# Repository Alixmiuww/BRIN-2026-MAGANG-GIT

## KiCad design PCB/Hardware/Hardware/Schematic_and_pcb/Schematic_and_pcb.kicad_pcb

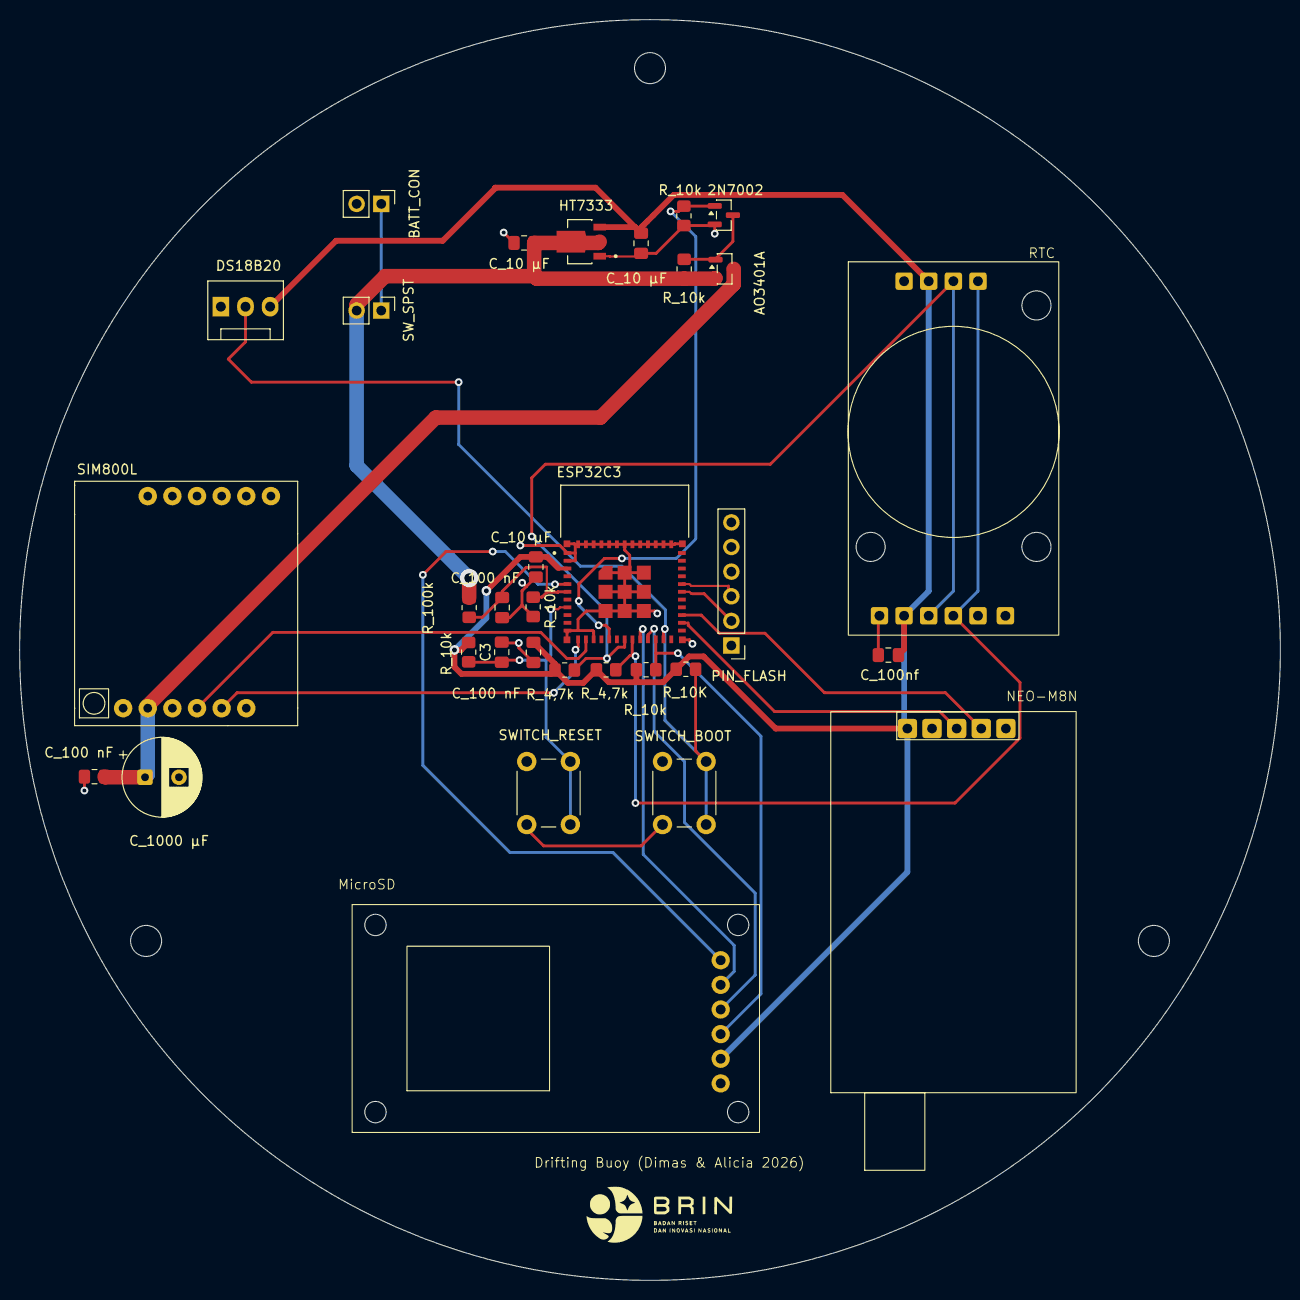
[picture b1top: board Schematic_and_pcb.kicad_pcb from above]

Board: 2 copper layers, 130.0 x 130.0 mm, 35 parts (0 on the bottom side), 22 nets.

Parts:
2N7002: 2N7002; SOT-23
AO3401A: AO3401A; SOT-23
BATT_CON: Battery Conn; PinHeader_1x02_P2.54mm_Vertical
C3: 1 µF; C_0805_2012Metric_Pad1.18x1.45mm_HandSolder
C_10 µF, C_10 µF#2, C_10 µF#3: 10 µF; C_0805_2012Metric_Pad1.18x1.45mm_HandSolder
C_100 nF, C_100 nF#2, C_100 nF#3, C_100nf: 100 nF; C_0805_2012Metric_Pad1.18x1.45mm_HandSolder
C_1000 µF: 1000 µF; CP_Radial_D8.0mm_P3.50mm
DS18B20: DS18B20; FanPinHeader_1x03_P2.54mm_Vertical
ESP32C3: ESP32-C3-MINI-1-N4; XCVR_ESP32-C3-MINI-1-N4
H1, H2, H3: MountingHole; MountingHole_3.2mm_M3
HT7333: HT7333; IC_HT7333
MicroSD: modul sdcard
NEO-M8N: Untitled
PIN_FLASH: PIN_FLASH; PinHeader_1x06_P2.54mm_Vertical
RTC: DS3231M; DS3231
R_4,7k, R_4,7k#2: 4.7 kΩ; R_0805_2012Metric_Pad1.20x1.40mm_HandSolder
R_10K, R_10k, R_10k#3: 10k; R_0805_2012Metric_Pad1.20x1.40mm_HandSolder
R_10k#2, R_100k: 100 kΩ; R_0805_2012Metric_Pad1.20x1.40mm_HandSolder
R_10k#4, R_10k#5: 10 kΩ; R_0805_2012Metric_Pad1.20x1.40mm_HandSolder
SIM800L: SIM800L-CORE
SWITCH_BOOT: SW_BOOT; SW_PUSH_6mm
SWITCH_RESET: SW_RESET; SW_PUSH_6mm
SW_SPST: SW_SPST; PinHeader_1x02_P2.54mm_Vertical

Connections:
+3.3V: C_10 µF#2.1, C_10 µF#3.1, C_100 nF#3.1, C_100nf.2, DS18B20.3 (V_{DD}), ESP32C3.3 (3V3), HT7333.3 (VOUT), MicroSD.VCC, NEO-M8N.VCC, RTC.VCC, R_4,7k.1, R_4,7k#2.1, R_10K.1, R_10k.1, R_10k#3.1
/I2C.SCL: ESP32C3.19 (IO5), RTC.SCL, R_4,7k#2.2
/I2C.SDA: ESP32C3.18 (IO4), RTC.SDA, R_4,7k.2
/MCU_Core/EN: C3.1, ESP32C3.8 (EN), R_10k#3.2, SWITCH_RESET.1
/MCU_Core/GATE_CTRL: 2N7002.1 (G), ESP32C3.16 (IO10), R_10k#5.1
/MCU_Core/GPS_RX_MCU: ESP32C3.26 (IO18), NEO-M8N.TXD
/MCU_Core/GPS_TX_MCU: ESP32C3.27 (IO19), NEO-M8N.RXD
/MCU_Core/MCU_BOOT: DS18B20.2 (DQ), ESP32C3.23 (IO9), R_10K.2, SWITCH_BOOT.1
/MCU_Core/RXD0: ESP32C3.31 (TXD0), PIN_FLASH.3
/MCU_Core/SD_CS: ESP32C3.5 (IO2), MicroSD.CS (~CS)
/MCU_Core/SIM_RX_MCU: ESP32C3.12 (IO0), SIM800L.5 (TXD)
/MCU_Core/SIM_TX_MCU: ESP32C3.13 (IO1), SIM800L.4 (RXD)
/MCU_Core/SPI_MISO: ESP32C3.22 (IO8), MicroSD.MISO, R_10k.2
/MCU_Core/SPI_MOSI: ESP32C3.21 (IO7), MicroSD.MOSI
/MCU_Core/SPI_SCK: ESP32C3.20 (IO6), MicroSD.SCK
/MCU_Core/TXD0: ESP32C3.30 (RXD0), PIN_FLASH.2
/MCU_Core/VBAT_ADC: C_100 nF.1, ESP32C3.6 (IO3), R_10k#2.1, R_100k.2
GND: 2N7002.2 (S), BATT_CON.2, C3.2, C_10 µF.2, C_10 µF#2.2, C_10 µF#3.2, C_100 nF.2, C_100 nF#2.2, C_100 nF#3.2, C_100nf.1, C_1000 µF.2, DS18B20.1 (GND), ESP32C3.1 (GND), ESP32C3.2 (GND), ESP32C3.11 (GND), ESP32C3.14 (GND), ESP32C3.36 (GND), ESP32C3.37 (GND), ESP32C3.38 (GND), ESP32C3.39 (GND), ESP32C3.40 (GND), ESP32C3.41 (GND), ESP32C3.42 (GND), ESP32C3.43 (GND), ESP32C3.44 (GND), ESP32C3.45 (GND), ESP32C3.46 (GND), ESP32C3.47 (GND), ESP32C3.48 (GND), ESP32C3.49_1 (GND), ESP32C3.49_2 (GND), ESP32C3.49_3 (GND), ESP32C3.49_4 (GND), ESP32C3.49_5 (GND), ESP32C3.49_6 (GND), ESP32C3.49_7 (GND), ESP32C3.49_8 (GND), ESP32C3.49_9 (GND), ESP32C3.50 (GND), ESP32C3.51 (GND), ESP32C3.52 (GND), ESP32C3.53 (GND), HT7333.1 (GND), MicroSD.GND, NEO-M8N.GND, PIN_FLASH.5, PIN_FLASH.6, RTC.GND, R_10k#2.2, R_10k#5.2, SIM800L.6 (GND), SWITCH_BOOT.2, SWITCH_RESET.2
unnamed: BATT_CON.1, SW_SPST.1 (A)
unnamed: 2N7002.3 (D), AO3401A.1 (G), R_10k#4.1
V_BAT: AO3401A.2 (S), C_10 µF.1, HT7333.2 (VIN), R_10k#4.2, R_100k.1, SW_SPST.2 (B)
V_SWITCHED: AO3401A.3 (D), C_100 nF#2.1, C_1000 µF.1, SIM800L.2 (VCC)

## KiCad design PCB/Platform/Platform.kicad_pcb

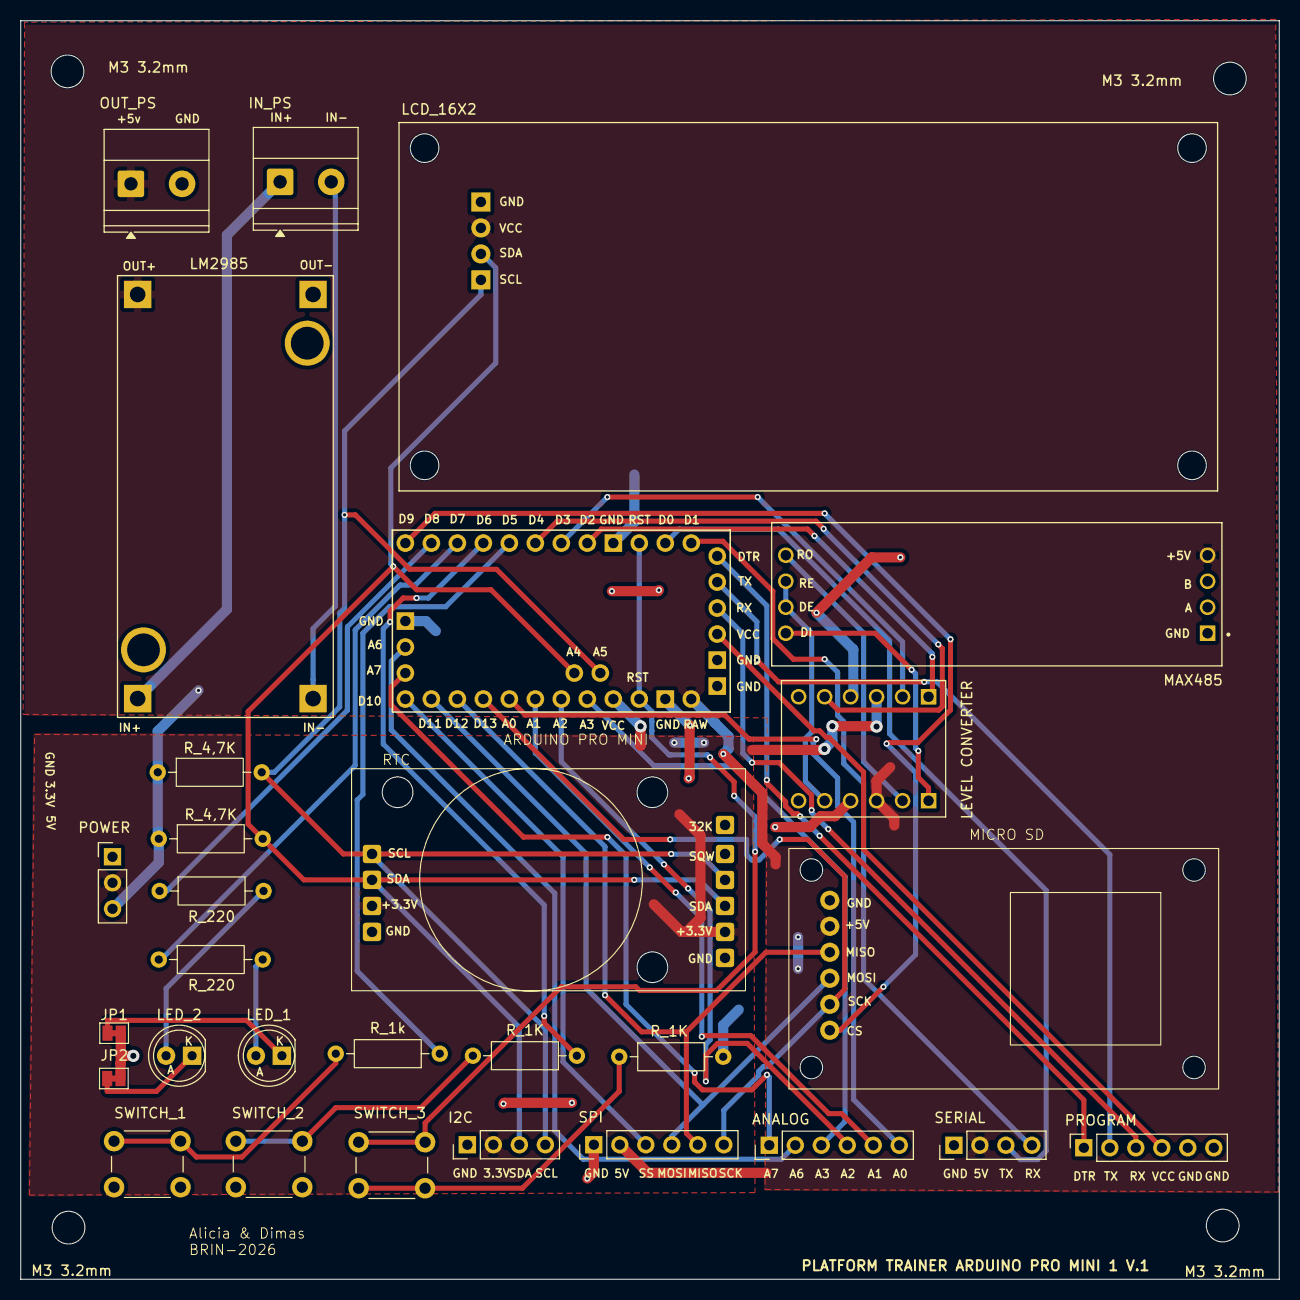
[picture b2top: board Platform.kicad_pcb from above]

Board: 2 copper layers, 123.0 x 123.0 mm, 33 parts (0 on the bottom side), 42 nets.

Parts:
A2: Clone_Pro_Mini_Socket
ANALOG: Pin_Analog; PinHeader_1x06_P2.54mm_Vertical
I2C: Pin_I2C_eksternal; PinHeader_1x04_P2.54mm_Vertical
IN_PS: Conn_01x02_Pin; TerminalBlock_Phoenix_MKDS-1,5-2_1x02_P5.00mm_Horizontal
JP1, JP2: SolderJumper_2_Bridged; SolderJumper-2_P1.3mm_Bridged_Pad1.0x1.5mm
LCD_16X2: Pin_LCD; MODULE_LCD-16X2
LED_1, LED_2: LED; LED_D5.0mm
LEVEL CONVERTER: BOB-12009; CONV_BOB-12009
LM2985: LM2596; CONV_MC00100
M3 3.2mm, M3 3.2mm#2, M3 3.2mm#3, M3 3.2mm#4: MountingHole_3.2mm_M3
MAX485: MAX485_MODULE_5V_LOGIC_TLL_TO_RS-485_CONVERTER; MODULE_MAX485_MODULE_5V_LOGIC_TLL_TO_RS-485_CONVERTER
MICRO SD: MICRO SDCARD; modul sdcard
OUT_PS: Conn_01x02_Pin; TerminalBlock_Phoenix_MKDS-1,5-2_1x02_P5.00mm_Horizontal
POWER: PWR External; PinHeader_1x03_P2.54mm_Vertical
PROGRAM: Program; PinSocket_1x06_P2.54mm_Vertical
RTC: PIN_RTC; DS3231
R_1K, R_1K#2, R_1k: 1kΩ; R_Axial_DIN0207_L6.3mm_D2.5mm_P10.16mm_Horizontal
R_4,7K, R_4,7K#2: 4.7k; R_Axial_DIN0207_L6.3mm_D2.5mm_P10.16mm_Horizontal
R_220, R_220#2: 220Ω; R_Axial_DIN0207_L6.3mm_D2.5mm_P10.16mm_Horizontal
SERIAL: Pin_SERIAL; PinHeader_1x04_P2.54mm_Vertical
SPI: Pin_SPI_1; PinHeader_1x06_P2.54mm_Vertical
SWITCH_1, SWITCH_2: SW_Push; SW_PUSH_6mm
SWITCH_3: RST; SW_PUSH_6mm

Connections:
+3.3V: A2.Vcc1 (Vcc), I2C.2, LEVEL CONVERTER.LV, POWER.2, RTC.VCC (Pin_2)
+5V: A2.RAW, LCD_16X2.VCC (Pin_2), LEVEL CONVERTER.HV, LM2985.OUT+, MAX485.4 (VCC), MICRO SD.VCC (Pin_3), OUT_PS.1, POWER.3, R_4,7K.1, R_4,7K#2.1, SERIAL.2, SPI.2
/A0: A2.A0, ANALOG.6
/A1: A2.A1, ANALOG.5
/A2: A2.A2, ANALOG.4
/A3: A2.A3, ANALOG.3
/A6: A2.A6, ANALOG.2
/A7: A2.A7, ANALOG.1
/I2C_UART_BUS.RX: A2.D1 (D1/TX), SERIAL.4
/I2C_UART_BUS.SCL: A2.A5 (A5/SCL), I2C.4, LCD_16X2.SCL (Pin_4), RTC.SCL (Pin_4), R_4,7K#2.2
/I2C_UART_BUS.SDA: A2.A4 (A4/SDA), I2C.3, LCD_16X2.SDA (Pin_3), RTC.SDA (Pin_3), R_4,7K.2
/I2C_UART_BUS.TX: A2.D0 (D0/RX), SERIAL.3
/IO_BUS.BTN1: A2.D5, R_1k.1
/IO_BUS.BTN2: A2.D6, R_1K.1
/IO_BUS.LED1: A2.D7, R_220#2.1
/IO_BUS.LED2: A2.D8, R_220.1
/RS485_CTRL: A2.D4, LEVEL CONVERTER.LV3
/RS485_HV1: LEVEL CONVERTER.HV1, MAX485.HV1 (RO)
/RS485_HV2: LEVEL CONVERTER.HV2, MAX485.HV2 (DI)
/RS485_HV3: LEVEL CONVERTER.HV3, MAX485.HV3 (DE)
/RS485_RX: A2.D2 (D2_INT0), LEVEL CONVERTER.LV1
/RS485_TX: A2.D3 (D3_INT1), LEVEL CONVERTER.LV2
/RST: A2.RST1 (RESET), A2.RST2 (RESET), SWITCH_3.1
/SPI_BUS.MISO: A2.D12 (D12_MISO), MICRO SD.MISO (Pin_6), SPI.5
/SPI_BUS.MOSI: A2.D11 (D11_MOSI), MICRO SD.MOSI (Pin_2), SPI.4
/SPI_BUS.SCK: A2.D13 (D13_SCK), MICRO SD.SCK (Pin_4), SPI.6
/SPI_BUS.SD_CS: A2.D9, MICRO SD.CS (Pin_1)
/SPI_BUS.SS: A2.D10 (D10_CS), SPI.3
/V_RAW: IN_PS.1, LM2985.IN+
GND: A2.GND1 (GND), A2.GND2 (GND), A2.GND3 (GND), A2.GND4 (GND), A2.GND5 (GND), I2C.1, JP1.2 (B), JP2.2 (B), LCD_16X2.GND (Pin_1), LEVEL CONVERTER.GND_1 (GND), LEVEL CONVERTER.GND_2 (GND), LM2985.OUT-, MAX485.1 (GND), MICRO SD.GND (Pin_5), OUT_PS.2, POWER.1, PROGRAM.5, PROGRAM.6, RTC.GND (Pin_1), R_1K#2.2, SERIAL.1, SPI.1, SWITCH_1.2, SWITCH_2.2
unnamed: A2.DTR (~DTR), PROGRAM.1
unnamed: LED_1.2 (A), R_220#2.2
unnamed: JP1.1 (A), LED_1.1 (K)
unnamed: LED_2.2 (A), R_220.2
unnamed: JP2.1 (A), LED_2.1 (K)
unnamed: A2.TXO, PROGRAM.2
unnamed: A2.RXI, PROGRAM.3
unnamed: A2.Vcc2 (Vcc), PROGRAM.4
unnamed: IN_PS.2, LM2985.IN-
unnamed: R_1k.2, SWITCH_1.1
unnamed: R_1K.2, SWITCH_2.1
unnamed: R_1K#2.1, SWITCH_3.2

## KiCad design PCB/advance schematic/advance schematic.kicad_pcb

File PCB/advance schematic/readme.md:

# ESP32 Controller — Schematic Documentation

## 1. Deskripsi Proyek

Proyek ini merupakan pengembangan rangkaian kontroler berbasis **ESP32-DevKitC-32E** yang menggunakan dua modul joystick analog, beberapa tombol kontrol, sensor GY-521 (MPU6050), LED RGB, serta rangkaian pemantauan tegangan baterai.

Rangkaian dirancang sebagai perangkat input untuk membaca pergerakan joystick, menerima perintah dari tombol, dan menyediakan data sensor untuk kebutuhan sistem kendali elektronik, seperti robot atau kendaraan berbasis mikrokontroler.

## 2. Fitur Utama

- **Dual Analog Joystick:** Membaca input sumbu X dan Y dari dua modul joystick.
- **Button Control:** Menyediakan tombol untuk kontrol drop, pickup, peningkatan kecepatan, penurunan kecepatan, dan pemilihan mode.
- **IMU Sensor:** Menggunakan GY-521 berbasis MPU6050 untuk membaca percepatan dan kecepatan sudut.
- **Battery Voltage Monitoring:** Menyediakan rangkaian pembagi tegangan untuk membaca tegangan baterai melalui ADC ESP32.
- **RGB LED Indicator:** Menyediakan indikator visual melalui LED RGB.
- **ESP32 Microcontroller:** Bertindak sebagai pusat pembacaan input dan pemrosesan data kontrol.

## 3. Komponen yang Digunakan

| Komponen | Fungsi |
|---|---|
| ESP32-DevKitC-32E | Mikrokontroler utama |
| 2× Joystick Module | Input analog sumbu X dan Y |
| 6× Push Button | Input perintah kontrol |
| GY-521 (MPU6050) | Sensor gerak berbasis IMU |
| LED RGB | Indikator status |
| Resistor 10 kΩ | Jaringan tombol dan pembagi tegangan |
| Resistor 100 kΩ | Pembagi tegangan pemantauan baterai |
| Konektor baterai | Input tegangan baterai |
| Sakelar | Pengendalian jalur rangkaian sesuai skematik |

## 4. Pemetaan Pin ESP32

### A. Input Joystick

| Sinyal | GPIO ESP32 |
|---|---:|
| JOY.VRx1 | GPIO 33 |
| JOY.VRy1 | GPIO 32 |
| JOY.VRx2 | GPIO 35 |
| JOY.VRy2 | GPIO 34 |

GPIO 32, 33, 34, dan 35 digunakan untuk membaca sinyal analog dari kedua joystick. GPIO 34 dan GPIO 35 merupakan pin input-only sehingga sesuai untuk pembacaan ADC.

### B. Tombol Kontrol

| Sinyal | GPIO ESP32 | Fungsi |
|---|---:|---|
| CONTROL.drop | GPIO 13 | Perintah drop |
| CONTROL.plck | GPIO 14 | Perintah pickup |
| CONTROL.up | GPIO 26 | Menaikkan kecepatan |
| CONTROL.down | GPIO 25 | Menurunkan kecepatan |
| SW.mode.joy1 | GPIO 18 | Pemilihan mode joystick |
| SW.mode.sensor | GPIO 19 | Pemilihan mode sensor |

**Catatan:** Pemetaan pin mengikuti label jaringan pada skematik. Pastikan konfigurasi pin pada program sesuai dengan hasil akhir desain PCB.

### C. Sensor GY-521 (MPU6050)

| Sinyal | Koneksi |
|---|---|
| VCC | +5 V sesuai skematik |
| GND | GND |
| SDA | Jalur I²C SDA |
| SCL | Jalur I²C SCL |
| AD0 | Tidak terhubung |
| INT | Tidak terhubung |
| XCL dan XDA | Tidak terhubung |

Jalur SDA dan SCL dihubungkan ke GPIO ESP32 yang ditentukan dalam konfigurasi perangkat lunak. Pin AD0 yang tidak terhubung umumnya membuat alamat I²C MPU6050 berada pada `0x68`, tetapi kondisi pin perlu dipastikan pada modul yang digunakan.

### D. LED RGB

LED RGB digunakan sebagai indikator status perangkat. Setiap kanal warna terhubung ke jalur GPIO melalui rangkaian pada skematik.

**Catatan:** Nomor GPIO untuk setiap kanal LED perlu dipastikan dari label net dan koneksi lengkap pada skematik sebelum diimplementasikan dalam kode.

### E. Pemantauan Tegangan Baterai

Rangkaian pemantauan tegangan menggunakan resistor pembagi tegangan untuk menyesuaikan tegangan baterai dengan rentang input ADC ESP32.

Nilai tegangan input dapat dihitung menggunakan:

`V_baterai = V_ADC × (R_atas + R_bawah) / R_bawah`

Rumus tersebut berlaku untuk pembagi tegangan standar, dengan `R_atas` terhubung dari baterai positif ke titik ADC dan `R_bawah` terhubung dari titik ADC ke GND.

**Penting:** Nilai resistor dan jalur pada skematik perlu diverifikasi. Pastikan tegangan yang masuk ke pin ADC tidak melebihi batas aman ESP32. Jika ingin mengukur tegangan baterai di atas rentang ADC, gunakan pembagi tegangan yang sesuai.

## 5. Prinsip Kerja Sistem

1. ESP32 dinyalakan melalui sumber daya yang sesuai.
2. Kedua joystick menghasilkan sinyal analog sesuai posisi sumbu X dan Y.
3. ESP32 membaca perubahan sinyal analog melalui ADC.
4. Tombol memberikan perintah digital untuk drop, pickup, pengaturan kecepatan, dan pemilihan mode.
5. Sensor MPU6050 menyediakan data percepatan dan kecepatan sudut melalui komunikasi I²C.
6. Rangkaian pembagi tegangan menyediakan sinyal yang mewakili tegangan baterai untuk dipantau ESP32.
7. Data input diproses oleh firmware untuk menentukan perintah kontrol dan status sistem.

## 6. Perangkat Lunak

Firmware dapat dikembangkan menggunakan Arduino IDE atau PlatformIO dengan framework Arduino.

Library yang dapat digunakan:
- `Arduino.h` — fungsi dasar ESP32.
- `Wire.h` — komunikasi I²C.
- Library MPU6050 yang kompatibel — pembacaan data IMU.

## 7. Catatan Desain dan Pengujian

Sebelum rangkaian diproduksi atau digunakan, lakukan pemeriksaan berikut:

- Verifikasi semua koneksi daya, GND, dan GPIO.
- Pastikan setiap tombol memiliki logika input yang sesuai dengan konfigurasi resistor.
- Periksa apakah resistor 10 kΩ pada jaringan tombol berfungsi sebagai pull-up atau pull-down sesuai kebutuhan.
- Pastikan tegangan keluaran joystick tidak melebihi batas ADC ESP32.
- Verifikasi konfigurasi pembagi tegangan baterai dan batas tegangan ADC.
- Pastikan LED RGB memiliki resistor pembatas arus yang sesuai untuk setiap kanal.
- Periksa alamat I²C MPU6050 dan jalur SDA/SCL menggunakan pemindaian I²C.
- Lakukan pemeriksaan ERC pada skematik dan DRC pada layout PCB sebelum fabrikasi.

## 8. Kesimpulan

Rangkaian ini dirancang sebagai kontroler berbasis ESP32 dengan input joystick analog, tombol digital, sensor IMU, indikator RGB, dan pemantauan tegangan baterai. Integrasi komponen tersebut memungkinkan ESP32 mengumpulkan berbagai input untuk diproses menjadi perintah kendali. Validasi koneksi daya, pemetaan GPIO, dan rangkaian ADC perlu dilakukan sebelum implementasi perangkat lunak dan pembuatan PCB.

## 9. Schematic Rancangan

## 10. PCB Rancangan

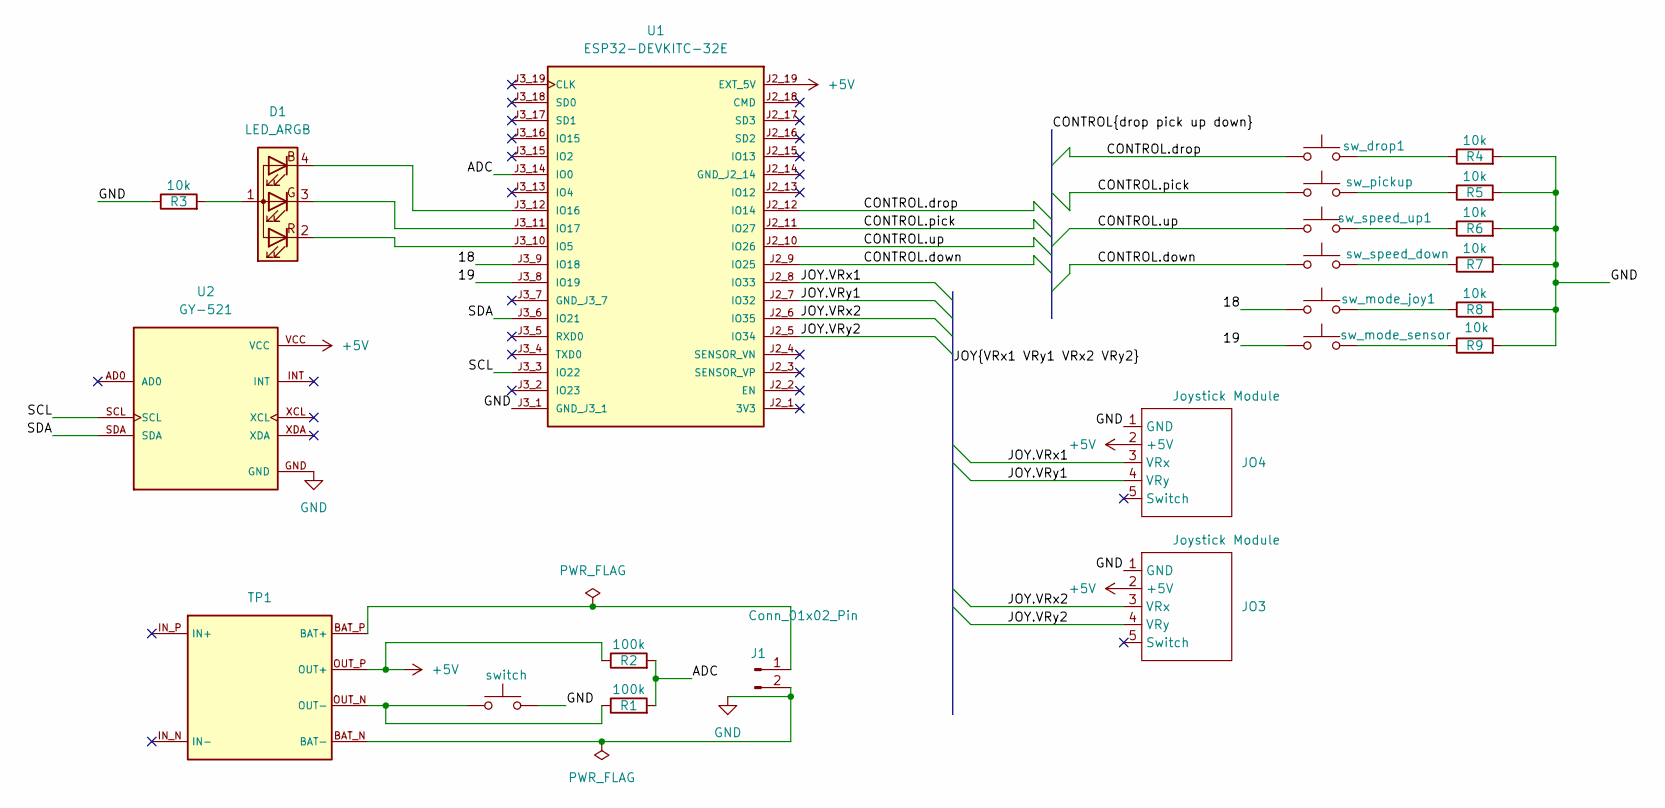
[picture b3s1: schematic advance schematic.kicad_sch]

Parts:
D1: LED_ARGB; LED_D5.0mm-4_RGB_Wide_Pins
J1: Conn_01x02_Pin; JST_EH_B2B-EH-A_1x02_P2.50mm_Vertical
JO3, JO4: Joystick Module; Module joystick
R1, R2: 100k; R_Axial_DIN0204_L3.6mm_D1.6mm_P1.90mm_Vertical
R3, R4, R5, R6, R7, R8, R9: 10k; R_Axial_DIN0204_L3.6mm_D1.6mm_P1.90mm_Vertical
SW2: sw_pickup; SW_PUSH_6mm
SW3: sw_speed_down; SW_PUSH_6mm
SW4: sw_mode_sensor; SW_PUSH_6mm
SW5: switch; SW_DIP_SPSTx01_Slide_6.7x4.1mm_W7.62mm_P2.54mm_LowProfile
TP1: MODULE_TP4056_MICRO-USB_CHARGER_-_1A
U1: ESP32-DEVKITC-32E; MODULE_ESP32-DEVKITC-32E; PARTREV 1.4
U2: GY-521; MODULE_GY-521; PARTREV NA
sw_drop1: SW_Push; SW_PUSH_6mm
sw_mode_joy1: SW_Push; SW_PUSH_6mm
sw_speed_up1: SW_Push; SW_PUSH_6mm

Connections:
+5V: JO3.2 (+5V), JO4.2 (+5V), R2.1, TP1.OUT_P (OUT+), U1.J2_19 (EXT_5V), U2.VCC
/18: U1.J3_9 (IO18), sw_mode_joy1.1
/19: SW4.1, U1.J3_8 (IO19)
/<NO NET>: D1.2 (RK), D1.4 (BK), U1.J3_10 (IO5), U1.J3_12 (IO16)
/ADC: R1.2, R2.2, U1.J3_14 (IO0)
/CONTROL.down: SW3.1, U1.J2_9 (IO25)
/CONTROL.drop: U1.J2_12 (IO14), sw_drop1.1
/CONTROL.pick: SW2.1, U1.J2_11 (IO27)
/CONTROL.up: U1.J2_10 (IO26), sw_speed_up1.1
/JOY.VRx1: JO4.3 (VRx), U1.J2_8 (IO33)
/JOY.VRx2: JO3.3 (VRx), U1.J2_6 (IO35)
/JOY.VRy1: JO4.4 (VRy), U1.J2_7 (IO32)
/JOY.VRy2: JO3.4 (VRy), U1.J2_5 (IO34)
/SCL: U1.J3_3 (IO22), U2.SCL
/SDA: U1.J3_6 (IO21), U2.SDA
GND: J1.2, JO3.1 (GND), JO4.1 (GND), R3.1, R4.2, R5.2, R6.2, R7.2, R8.2, R9.2, SW5.2, TP1.BAT_N (BAT-), U1.J3_1 (GND_J3_1), U2.GND
unnamed: D1.1 (A), R3.2
unnamed: D1.3 (GK), U1.J3_11 (IO17)
unnamed: J1.1, TP1.BAT_P (BAT+)
unnamed: R4.1, sw_drop1.2
unnamed: R5.1, SW2.2
unnamed: R6.1, sw_speed_up1.2
unnamed: R7.1, SW3.2
unnamed: R8.1, sw_mode_joy1.2
unnamed: R9.1, SW4.2
unnamed: R1.1, SW5.1, TP1.OUT_N (OUT-)

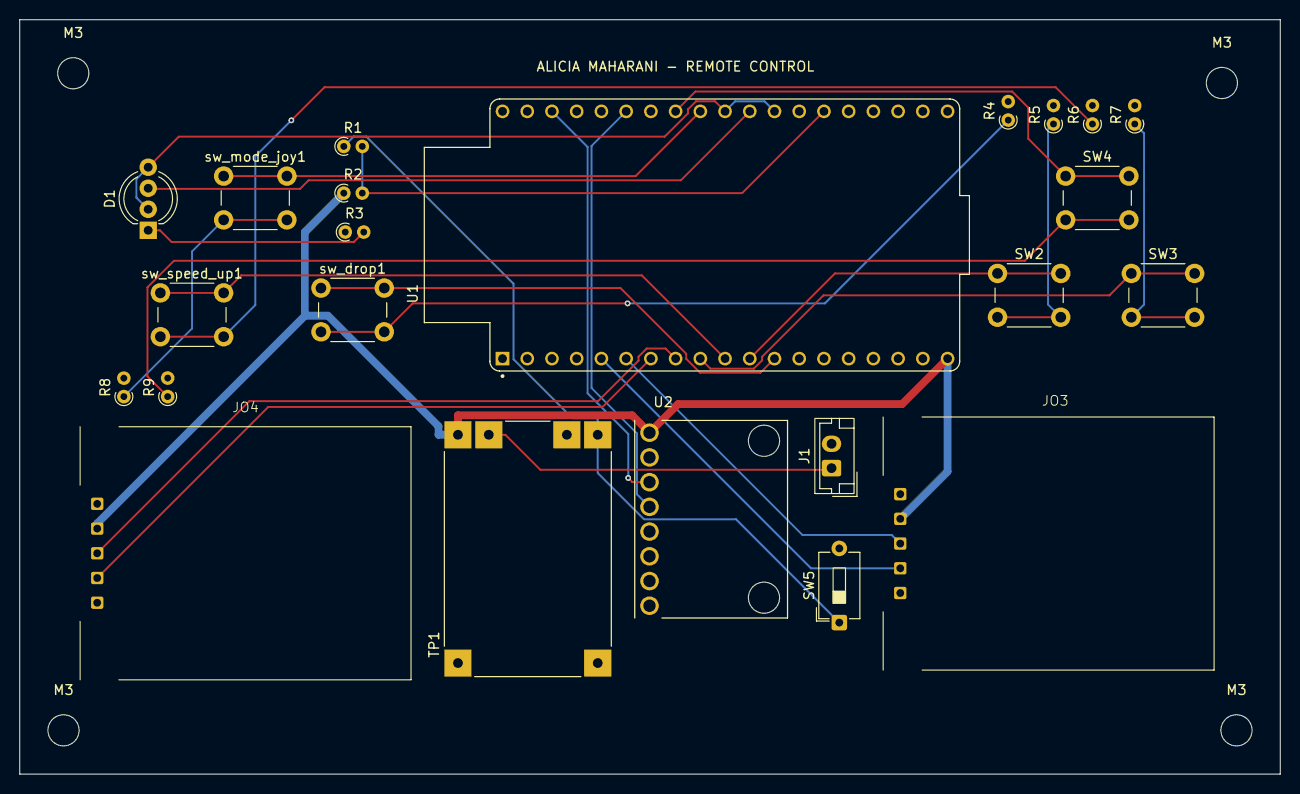
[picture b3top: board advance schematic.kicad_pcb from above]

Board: 2 copper layers, 129.5 x 77.5 mm, 27 parts (0 on the bottom side), 26 nets.

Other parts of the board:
M3, M3#2, M3#3, M3#4: MountingHole_3.2mm_M3

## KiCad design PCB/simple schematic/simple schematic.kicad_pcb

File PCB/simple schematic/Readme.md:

# Percobaan IC NE555 Timer

## 1. Deskripsi

Percobaan ini bertujuan untuk mempelajari penggunaan IC NE555 sebagai pembangkit sinyal pulsa (*pulse generator*). Rangkaian menggunakan konfigurasi astable atau osilator untuk menghasilkan sinyal keluaran secara periodik.

Sinyal keluaran dari pin 3 IC NE555 digunakan untuk mengendalikan LED sebagai indikator visual. Rangkaian menggunakan sumber tegangan 5 V, jaringan resistor, dan kapasitor untuk menentukan karakteristik sinyal yang dihasilkan.

## 2. Tujuan

- Memahami prinsip kerja IC NE555 Timer.
- Mempelajari konfigurasi rangkaian pembangkit pulsa.
- Memahami pengaruh resistor dan kapasitor terhadap frekuensi sinyal.
- Mengamati keluaran IC NE555 menggunakan LED.
- Memahami fungsi komponen pendukung pada rangkaian timer.

## 3. Alat dan Bahan

| No. | Komponen | Nilai / Tipe |
|---:|---|---|
| 1 | IC Timer | NE555P |
| 2 | Resistor R1 | 10 kΩ |
| 3 | Resistor R2 | 100 kΩ |
| 4 | Resistor R3 | 330 Ω |
| 5 | Kapasitor C1 | 10 µF |
| 6 | Kapasitor C2 | 100 nF |
| 7 | LED | 1 buah |
| 8 | Push button SW1 | 1 buah |
| 9 | Sumber tegangan | +5 V DC |
| 10 | Breadboard dan kabel jumper | Secukupnya |

## 4. Prinsip Kerja

IC NE555 dapat digunakan sebagai pembangkit sinyal pulsa dengan memanfaatkan proses pengisian dan pengosongan kapasitor.

Pada konfigurasi astable, tegangan kapasitor berubah secara periodik. Ketika tegangan kapasitor mencapai ambang tertentu, kondisi keluaran IC berubah sehingga menghasilkan sinyal pulsa berulang.

Sinyal keluaran tersebut dapat digunakan untuk mengendalikan LED sehingga perubahan kondisi keluaran dapat diamati secara visual.

## 5. Fungsi Komponen

| Komponen | Fungsi |
|---|---|
| NE555P | Menghasilkan sinyal pulsa |
| R1 (10 kΩ) | Bagian dari jaringan pengaturan dan pemicu rangkaian |
| R2 (100 kΩ) | Menentukan karakteristik pengisian dan pengosongan kapasitor sesuai konfigurasi |
| R3 (330 Ω) | Membatasi arus LED |
| C1 (10 µF) | Kapasitor timing yang memengaruhi periode sinyal |
| C2 (100 nF) | Kapasitor bypass atau decoupling untuk membantu menstabilkan suplai |
| SW1 | Tombol untuk mengubah kondisi rangkaian sesuai koneksinya |
| LED D1 | Indikator visual keluaran rangkaian |
| J1 | Konektor sumber daya +5 V dan GND |

## 6. Pin IC NE555

| Pin | Nama | Fungsi |
|---:|---|---|
| 1 | GND | Ground rangkaian |
| 2 | TRIG | Pemicu keluaran |
| 3 | OUT | Keluaran sinyal pulsa |
| 4 | RESET | Mengatur ulang atau menonaktifkan operasi IC ketika ditarik LOW |
| 5 | CONT | Mengatur tegangan referensi internal |
| 6 | THRES | Mendeteksi ambang tegangan kapasitor |
| 7 | DISCH | Jalur pengosongan kapasitor |
| 8 | VCC | Tegangan suplai positif |

## 7. Langkah Pengujian

1. Rakit rangkaian sesuai dengan skematik.
2. Pastikan seluruh koneksi IC NE555 sesuai dengan nomor pin.
3. Hubungkan sumber tegangan +5 V dan GND.
4. Amati kondisi LED setelah rangkaian diberi daya.
5. Tekan push button dan amati perubahan kondisi rangkaian.
6. Jika tersedia osiloskop, ukur sinyal keluaran pada pin 3 untuk mengamati bentuk gelombang, frekuensi, dan duty cycle.
7. Catat hasil pengamatan dan bandingkan dengan karakteristik rangkaian yang direncanakan.

## 8. Hasil yang Diharapkan

- IC NE555 bekerja sesuai konfigurasi rangkaiannya.
- Sinyal keluaran dapat diamati pada pin 3.
- LED menunjukkan perubahan kondisi sesuai sinyal keluaran.
- Pengukuran menggunakan osiloskop memperlihatkan bentuk gelombang keluaran yang sesuai dengan konfigurasi rangkaian.

## 9. Kesimpulan

Percobaan ini memperkenalkan penggunaan IC NE555 sebagai pembangkit sinyal pulsa. Resistor dan kapasitor berperan dalam menentukan karakteristik waktu rangkaian, sedangkan LED digunakan sebagai indikator keluaran. Pengukuran menggunakan osiloskop dapat membantu mengetahui frekuensi, periode, dan duty cycle sinyal secara lebih akurat.

## 10. Schematic Rangkaian 

## 11. PCB Rangkaian

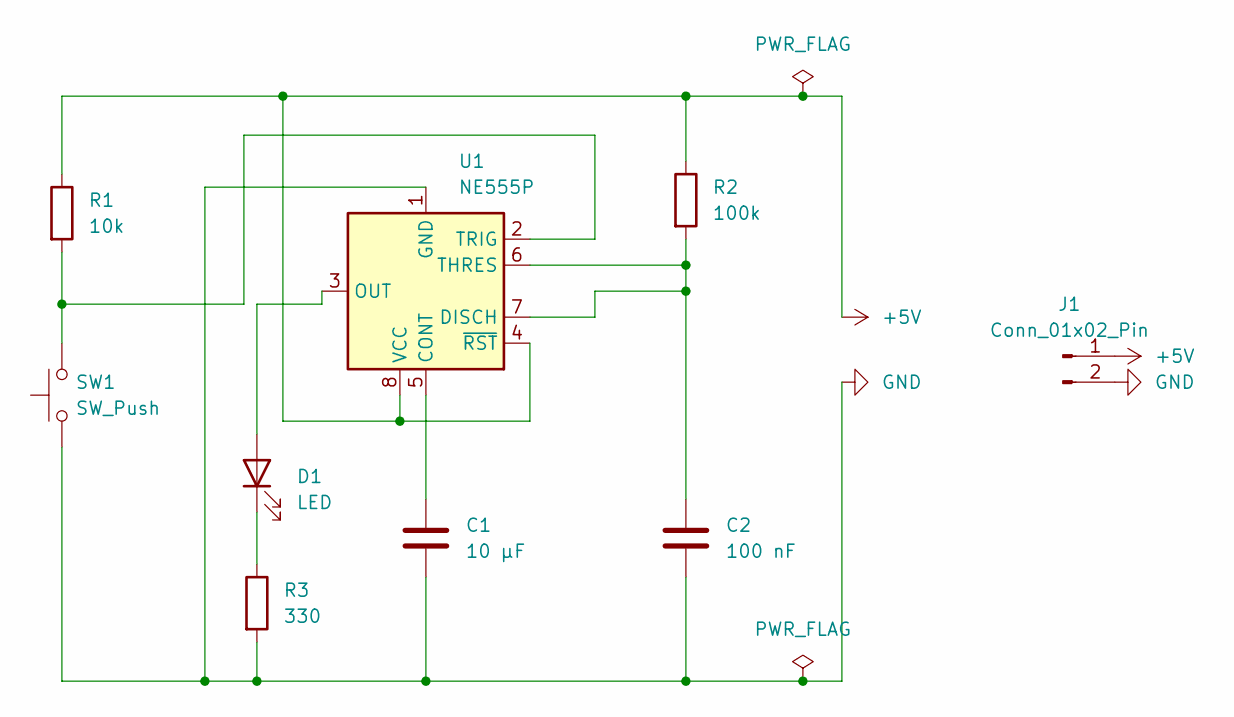
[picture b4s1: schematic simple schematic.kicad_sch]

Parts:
C1: 10 µF; CP_Radial_D6.3mm_P2.50mm
C2: 100 nF; C_Disc_D4.3mm_W1.9mm_P5.00mm
D1: LED; LED_D3.0mm
J1: Conn_01x02_Pin; JST_EH_B2B-EH-A_1x02_P2.50mm_Vertical
R1: 10k; R_Axial_DIN0204_L3.6mm_D1.6mm_P7.62mm_Horizontal
R2: 100k; R_Axial_DIN0204_L3.6mm_D1.6mm_P7.62mm_Horizontal
R3: 330; R_Axial_DIN0204_L3.6mm_D1.6mm_P7.62mm_Horizontal
SW1: SW_Push; SW_PUSH_6mm
U1: NE555P; DIP-8_W7.62mm

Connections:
+5V: J1.1, R1.1, R2.1, U1.4 (~RST), U1.8 (VCC)
GND: C1.2, C2.2, J1.2, R3.2, SW1.1, U1.1 (GND)
unnamed: D1.2 (A), U1.3 (OUT)
unnamed: D1.1 (K), R3.1
unnamed: C1.1, U1.5 (CONT)
unnamed: C2.1, R2.2, U1.6 (THRES), U1.7 (DISCH)
unnamed: R1.2, SW1.2, U1.2 (TRIG)

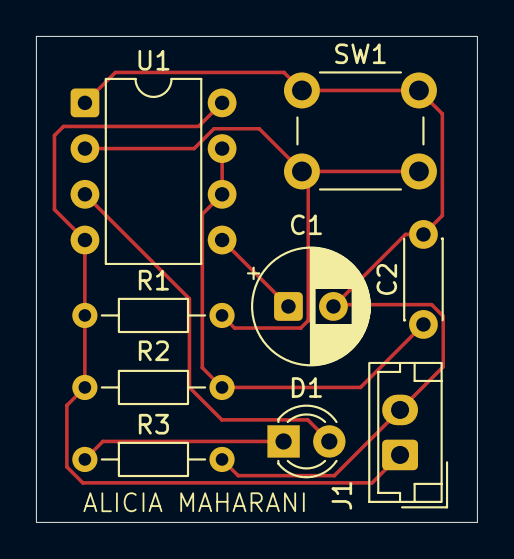
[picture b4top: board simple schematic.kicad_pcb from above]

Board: 2 copper layers, 24.5 x 27.0 mm, 9 parts (0 on the bottom side), 7 nets.
